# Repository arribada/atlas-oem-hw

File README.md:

# ATLAS OEM PCB

This is the PCB for the ATLAS OEM board.

## License

This project is licensed under the MIT License. See the LICENSE file for more details.

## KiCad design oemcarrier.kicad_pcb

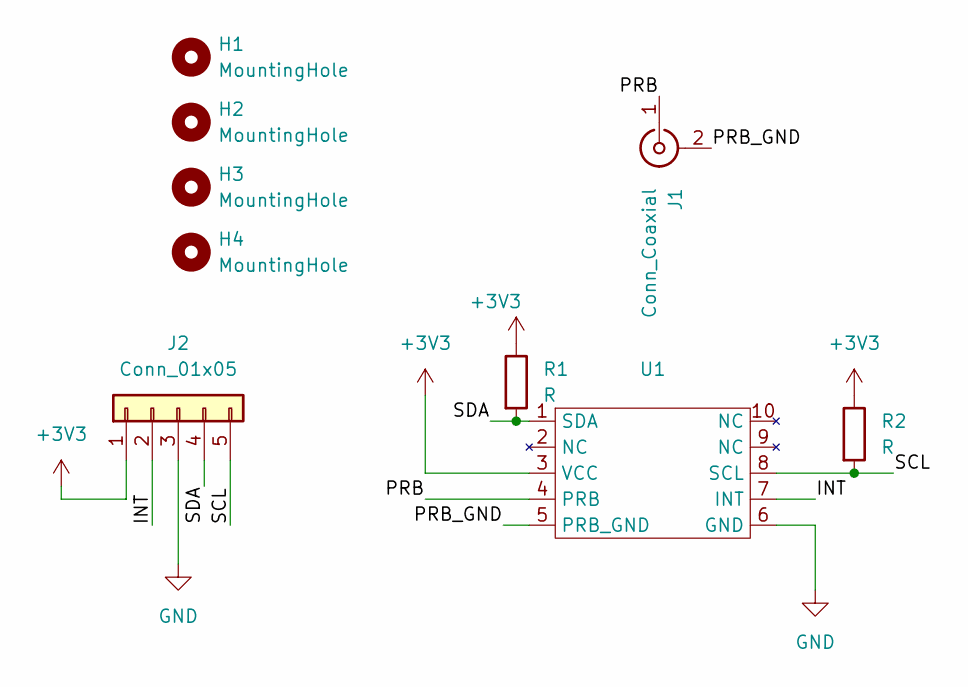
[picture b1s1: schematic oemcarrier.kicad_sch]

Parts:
H1, H2, H3, H4: MountingHole; MountingHole_2.2mm_M2_Pad
J1: Conn_Coaxial; SMA_Amphenol_132289_EdgeMount
J2: Conn_01x05; PinHeader_1x05_P2.54mm_Vertical
R1, R2: R; R_1206_3216Metric_Pad1.30x1.75mm_HandSolder
U1: OEM_PH

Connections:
+3V3: J2.1, R1.1, R2.1, U1.3 (VCC)
/INT: J2.2, U1.7 (INT)
/PRB: J1.1 (In), U1.4 (PRB)
/PRB_GND: J1.2 (Ext), U1.5 (PRB_GND)
/SCL: J2.5, R2.2, U1.8 (SCL)
/SDA: J2.4, R1.2, U1.1 (SDA)
GND: J2.3, U1.6 (GND)

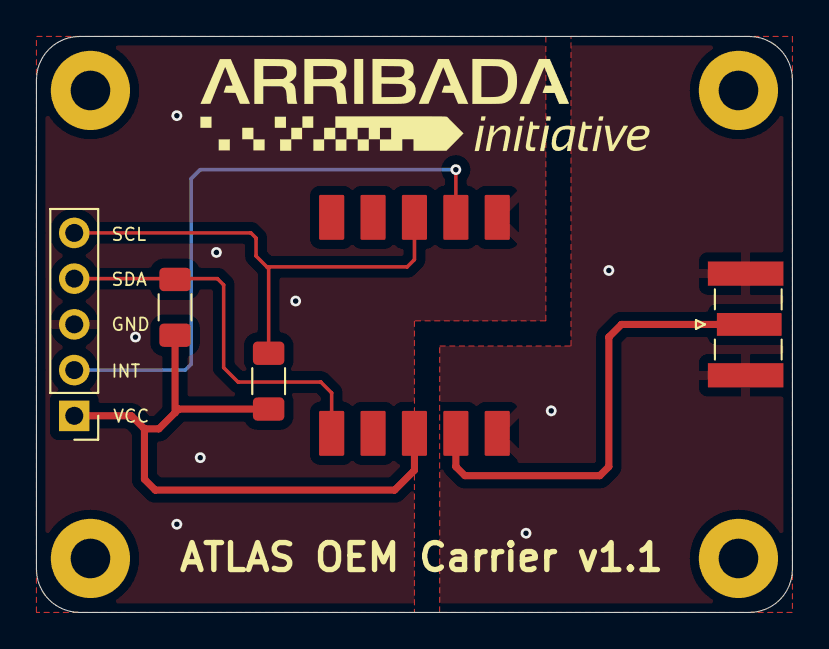
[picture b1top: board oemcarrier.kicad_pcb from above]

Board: 2 copper layers, 42.0 x 32.0 mm, 9 parts (0 on the bottom side), 7 nets.

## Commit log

2024-09-12 Initial commit
    Change-type: minor
